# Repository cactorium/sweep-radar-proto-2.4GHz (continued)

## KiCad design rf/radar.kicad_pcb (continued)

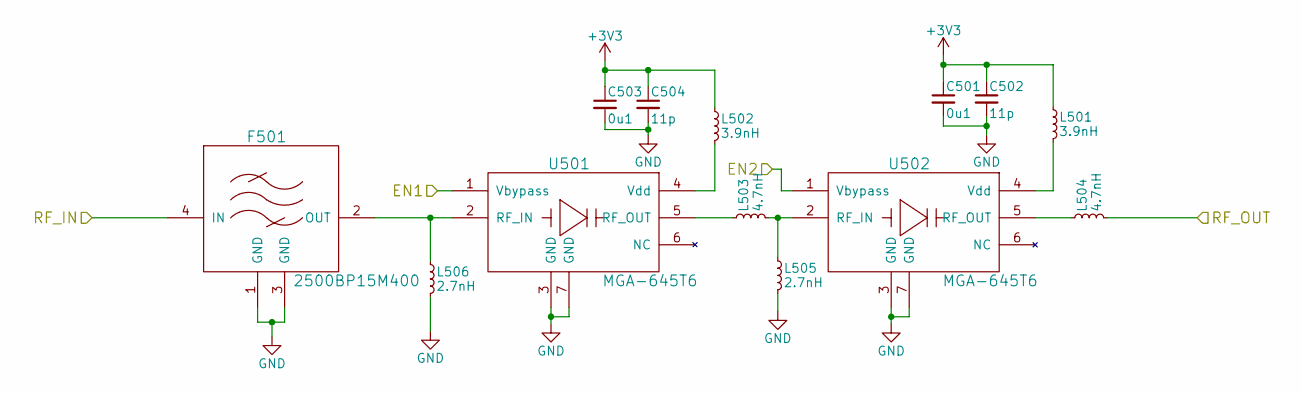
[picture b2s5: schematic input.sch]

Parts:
C501, C503: 0u1; C_0603_HandSoldering
C502, C504: 11p; C_0402
F501: 2500BP15M400
L501, L502: 3.9nH; C_0402
L503, L504: 4.7nH; C_0402
L505, L506: 2.7nH; C_0402
U501, U502: MGA-645T6

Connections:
+3V3: C501.1, C502.1, C503.1, C504.1, L501.1, L502.1; also elsewhere on the board
/INPUT_AMP/EN1: U501.1 (Vbypass); also elsewhere on the board
/INPUT_AMP/EN2: U502.1 (Vbypass); also elsewhere on the board
/INPUT_AMP/RF_IN: F501.4 (IN); also elsewhere on the board
/MIXER/RF_IN: L504.2; also elsewhere on the board
GND: C501.2, C502.2, C503.2, C504.2, F501.1 (GND), F501.3 (GND), L505.2, L506.2, U501.3 (GND), U501.7 (GND), U502.3 (GND), U502.7 (GND); also elsewhere on the board
unnamed: F501.2 (OUT), L506.1, U501.2 (RF_IN)
unnamed: L501.2, U502.4 (Vdd)
unnamed: L502.2, U501.4 (Vdd)
unnamed: L503.1, U501.5 (RF_OUT)
unnamed: L503.2, L505.1, U502.2 (RF_IN)
unnamed: L504.1, U502.5 (RF_OUT)

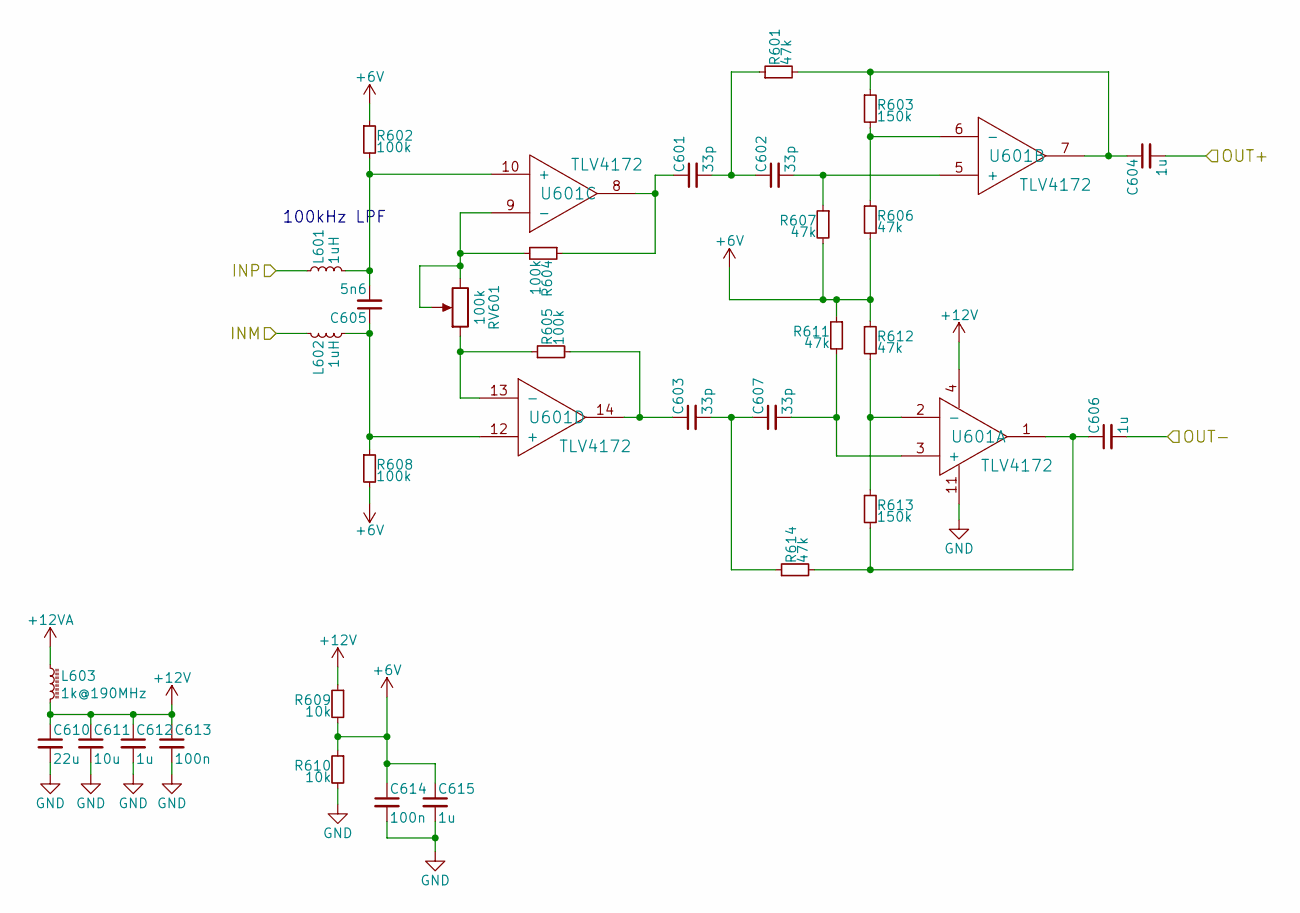
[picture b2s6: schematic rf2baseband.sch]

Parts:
C601, C602, C603, C607: 33p; C_0603_HandSoldering
C604, C606, C612, C615: 1u; C_0603_HandSoldering
C605: 5n6; C_0603_HandSoldering
C610: 22u; C_1210_HandSoldering
C611: 10u; C_0805_HandSoldering
C613, C614: 100n; C_0603_HandSoldering
L601, L602: 1uH; C_0402
L603: 1k@190MHz; C_0402
R601, R606, R607, R611, R612, R614: 47k; R_0603_HandSoldering
R602, R604, R605, R608: 100k; R_0402
R603, R613: 150k; R_0402
R609, R610: 10k; R_0402
RV601: 100k; RK09D113
U601: TLV4172; TSSOP-14_4.4x5mm_Pitch0.65mm

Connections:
+6V: C614.1, C615.1, R602.1, R606.2, R607.2, R608.2, R609.2, R610.1, R611.1, R612.1
+12V: C610.1, C611.1, C612.1, C613.1, L603.2, R609.1, U601.4
+12VA: L603.1; also elsewhere on the board
/BASEBAND/INM: L602.1; also elsewhere on the board
/BASEBAND/INP: L601.1; also elsewhere on the board
/BASEBAND/OUT+: C604.2; also elsewhere on the board
/BASEBAND/OUT-: C606.2; also elsewhere on the board
GND: C610.2, C611.2, C612.2, C613.2, C614.2, C615.2, R610.2, U601.11; also elsewhere on the board
unnamed: C601.1, R604.1, U601.8
unnamed: C601.2, C602.1, R601.1
unnamed: C602.2, R607.1, U601.5 (+)
unnamed: C603.1, R605.2, U601.14
unnamed: C603.2, C607.1, R614.1
unnamed: C604.1, R601.2, R603.1, U601.7
unnamed: C605.1, L602.2, R608.1, U601.12 (+)
unnamed: C605.2, L601.2, R602.2, U601.10 (+)
unnamed: C606.1, R613.2, R614.2, U601.1
unnamed: C607.2, R611.2, U601.3 (+)
unnamed: R603.2, R606.1, U601.6 (-)
unnamed: R604.2, RV601.2, RV601.3, U601.9 (-)
unnamed: R605.1, RV601.1, U601.13 (-)
unnamed: R612.2, R613.1, U601.2 (-)

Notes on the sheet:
100kHz LPF

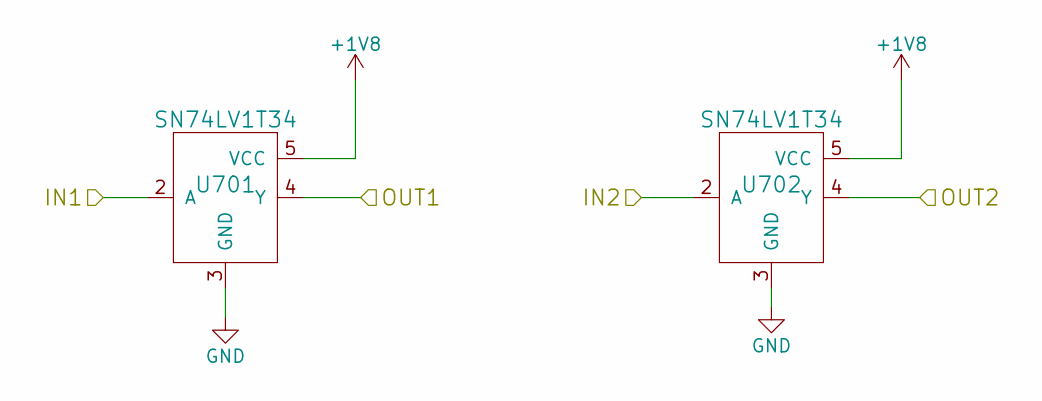
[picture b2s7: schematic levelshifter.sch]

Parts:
U701, U702: SN74LV1T34; SOT-23-5_HandSoldering

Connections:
+1V8: U701.5 (VCC), U702.5 (VCC); also elsewhere on the board
/INPUT_AMP/EN1: U701.4 (Y); also elsewhere on the board
/INPUT_AMP/EN2: U702.4 (Y); also elsewhere on the board
/LEVELSHIFTER/IN1: U701.2 (A); also elsewhere on the board
/LEVELSHIFTER/IN2: U702.2 (A); also elsewhere on the board
GND: U701.3 (GND), U702.3 (GND); also elsewhere on the board

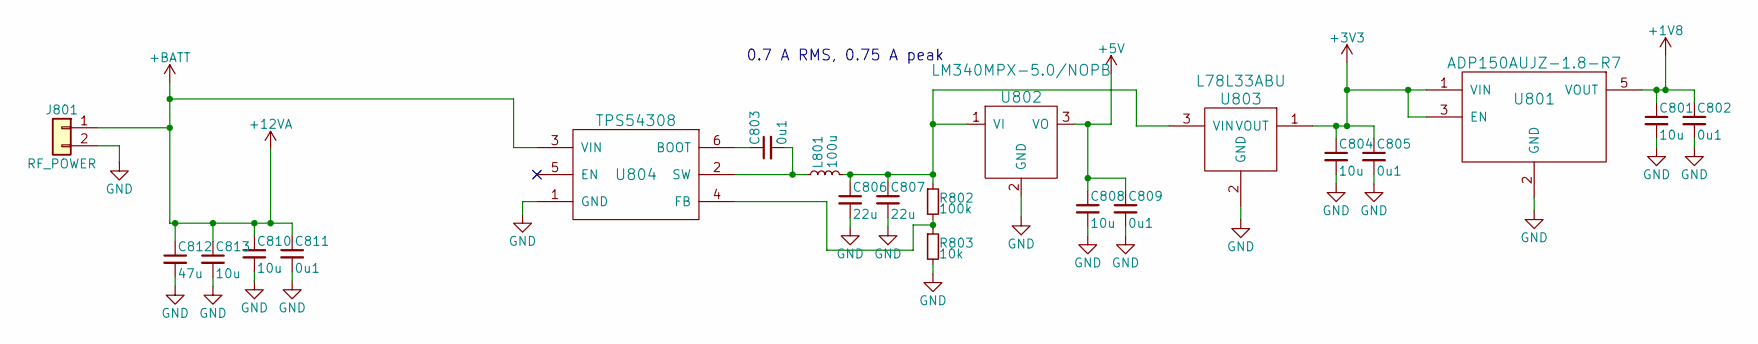
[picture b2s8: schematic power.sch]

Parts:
C801, C804, C808, C810, C813: 10u; C_0805_HandSoldering
C802, C803, C805, C809, C811: 0u1; C_0603_HandSoldering
C806, C807: 22u; C_1210_HandSoldering
C812: 47u; CP_Radial_D5.0mm_P2.00mm
J801: RF_POWER; Socket_Strip_Straight_1x02_Pitch2.54mm
L801: 100u; Murata_DG6050C
R802: 100k; R_0402
R803: 10k; R_0603_HandSoldering
U801: ADP150AUJZ-1.8-R7; TSOT-23
U802: LM340MPX-5.0/NOPB; SOT-223-3_TabPin2
U803: L78L33ABU; SOT-89-3_Handsoldering
U804: TPS54308; TI-SOT-23-6

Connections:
+1V8: C801.1, C802.1, U801.5 (VOUT); also elsewhere on the board
+3V3: C804.1, C805.1, U801.1 (VIN), U801.3 (EN), U803.1 (VOUT); also elsewhere on the board
+5V: C808.1, C809.1, U802.3 (VO); also elsewhere on the board
+12VA: C810.1, C811.1, C812.1, C813.1, J801.1, U804.3 (VIN); also elsewhere on the board
GND: C801.2, C802.2, C804.2, C805.2, C806.2, C807.2, C808.2, C809.2, C810.2, C811.2, C812.2, C813.2, J801.2, R803.2, U801.2 (GND), U802.2 (GND), U803.2 (GND), U804.1 (GND); also elsewhere on the board
unnamed: C803.1, U804.6 (BOOT)
unnamed: C803.2, L801.1, U804.2 (SW)
unnamed: C806.1, C807.1, L801.2, R802.1, U802.1 (VI), U803.3 (VIN)
unnamed: R802.2, R803.1, U804.4 (FB)

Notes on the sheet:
0.7 A RMS, 0.75 A peak

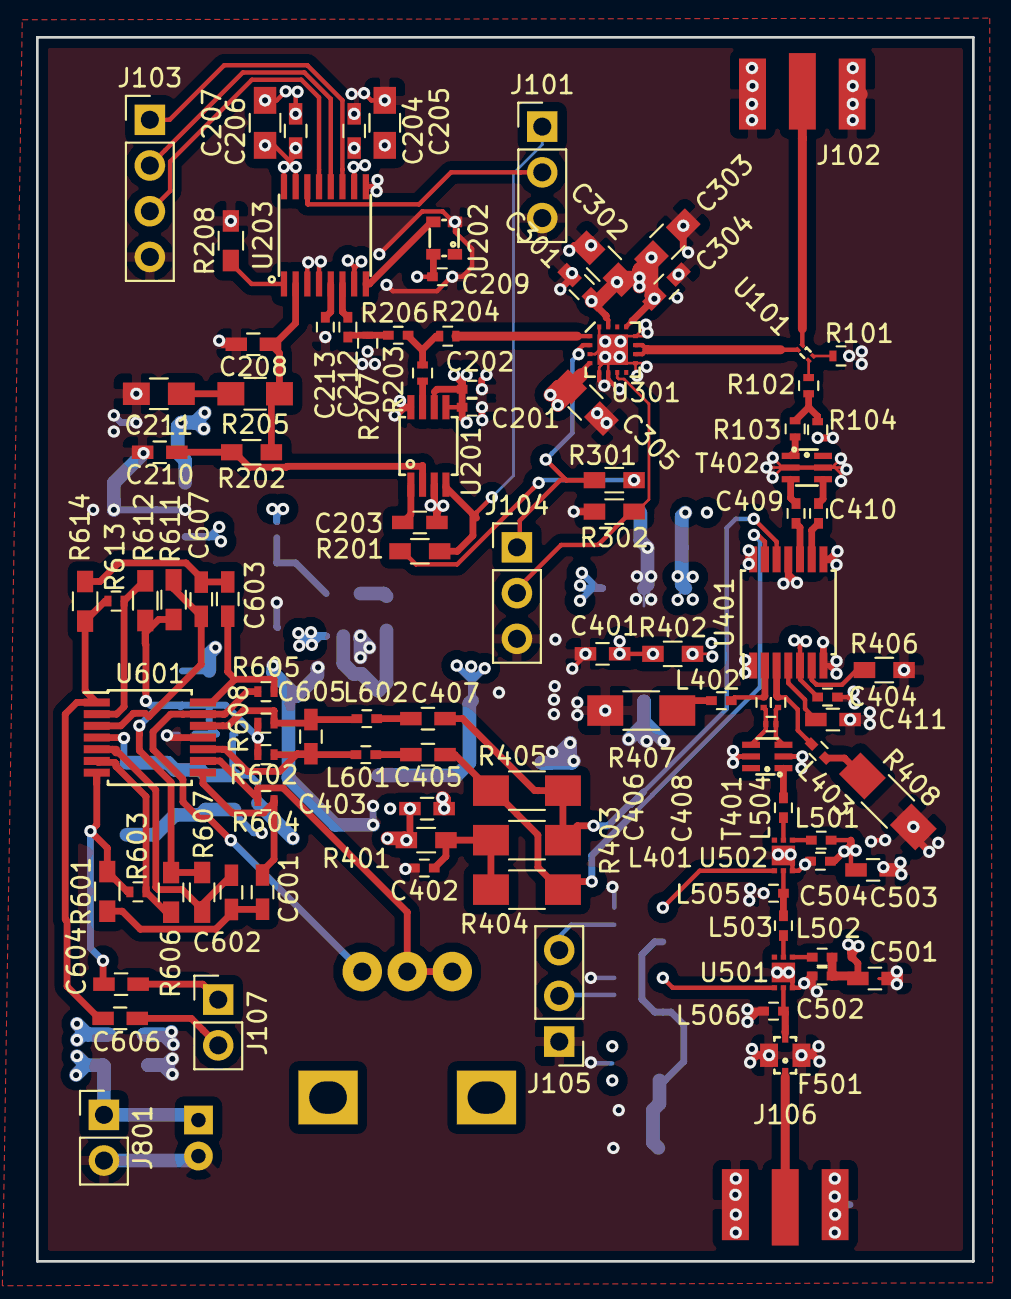
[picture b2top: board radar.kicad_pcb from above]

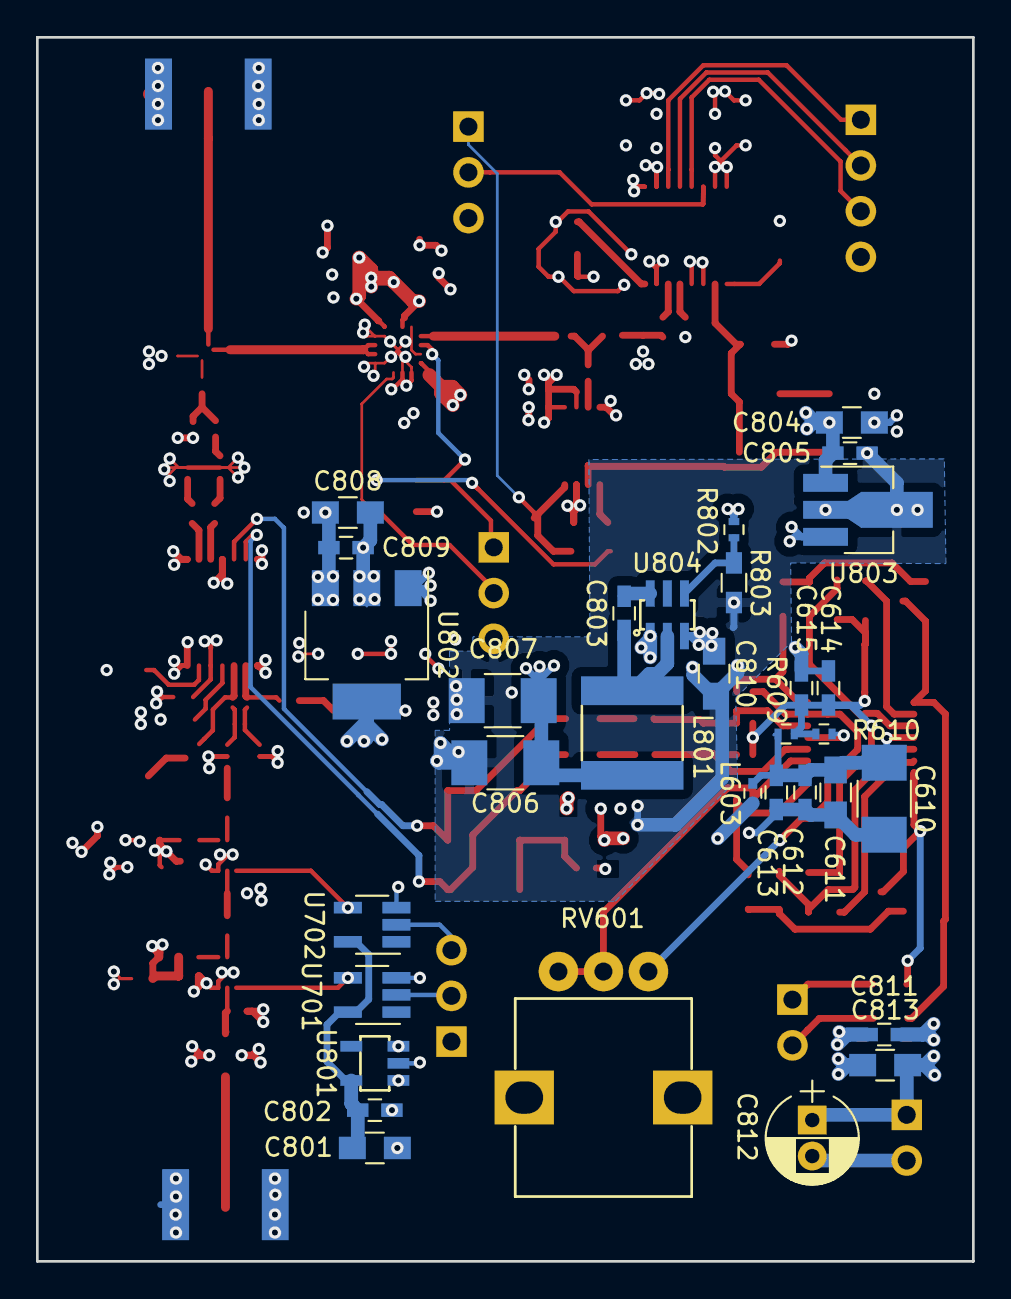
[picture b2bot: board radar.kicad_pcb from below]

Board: 4 copper layers, 52.0 x 68.0 mm, 137 parts (32 on the bottom side), 82 nets.

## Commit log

2017-10-14 All of it planned out; time to move to layout
2018-01-06 Schematic finished
2018-02-10 Assign a lot of footprints, fix l78l33abu part (input and output were reversed)
2018-03-31 Finished circuit layout (for the RF board)
2018-04-04 Switch signal conditioning to fully differential
2018-04-04 Move everything into RF folder
2018-04-08 Finish assigning component footprints
2018-04-12 Finish first revision layout
2018-04-13 Clean up PCB slightly
2018-04-13 Copy BOM generator from https://productize.be/kicad-bom-generation/
2018-04-14 Start work on ADC board
2018-04-14 Generate FPGA library file
2018-04-14 Small fixes; update Gerber
2018-04-14 Update Gerber for real
2018-04-14 Generate STM32 MCU library file
2018-04-14 Convert high pass from MFB to Sallen-Key; forgot about low input impedance for high pass MFB
2018-04-15 Massage vias to improve planes and swap out connectors to get more ground lines
2018-04-15 Add in STM32, connect up digital part of board
2018-04-17 Finish schematic TODO footprints
2018-04-17 Improve layout slightly
2018-04-17 Finish schematic and footprinting of digital board
2018-04-17 Fix voltage rails on op amp
2018-04-18 Add gain stage; hopefully ready to start layout now
2018-04-18 Line up connectors across both boards, spread out component footprints
2018-04-18 Finish digital layout
2018-04-19 Fix up some minor things
2018-04-19 Add via stitching to RF board
2018-04-19 Regenerate Gerbers
2018-04-19 Generate zip files
2018-04-19 Fix silkscreens and regenerate Gerbers
2018-04-24 Fix some more stuff I guess
2018-04-27 Test out soft start circuit
2018-04-27 Remove extra file
2018-04-27 Finish tweaking soft start circuits
2018-04-27 Rename to SPICE file extension
